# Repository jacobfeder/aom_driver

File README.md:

# 2-Tone AOM driver
This custom acousto-optic modulator (AOM) driver PCB is designed for generating short light pulses with enhanced isolation and power stability compared to traditional AOM configurations.

# Background
When generating light pulses with an AOM, two parameters that you may care about are the isolation and power stability.

The isolation (usually expressed in dB) is defined as $10*\log_{10}(P_{on} / P_{off})$, where $P_{on}$ is the transmitted optical power with the AOM enabled, and $P_{off}$ is the transmitted optical power with the AOM disabled. A low isolation means that even when the AOM is disabled, there is significant light leakage through the AOM, which can be undesirable for certain applications.

Power stability is the change in transmitted optical power as a function of time or AOM duty cycle. The active area of an AOM that the optical beam passes through is made of a material whose optical index of refraction changes with strain (acoustic waves), producing the desired beam diffraction. However, other variables, such as temperature, can impact the index of refraction and, therefore, the pointing stability of the beam.

Many traditional AOM drivers are used as follows:
- The driver produces a single frequency which is toggled on and off, often with relatively low isolation.
- The optical power is switched between being primarily concentrated in the 0th order diffraction peak (AOM disabled, RF off) and the 1st order peak (AOM enabled, RF on).

This configuration produces two undesirable effects. First, drivers with low isolation (RF power $P_{on}/P_{off}$) can limit the optical isolation of the AOM due to parasitic driving of the AOM with RF leakage. Second, when switching the RF drive on/off, there is a change in RF power dissipation in the AOM crystal, inducing a temperature change. This temperature change reduces the beam pointing stability and produces power fluctuations as a function of time and switching duty cycle.

# Overview

The 2-Tone AOM driver greatly mitigates isolation and power stability issues. Whereas traditional AOM drivers rapidly switch between an RF signal being on or off, this driver rapidly switches between two different RF frequencies. The optical power diffracted by the AOM with low-frequency drive should ideally be fiber coupled into a single-mode fiber and then used in your down-stream application. The optical power diffracted by the AOM with the high-frequency "dummy" drive should be sent into a beam-dump. If the power of the two frequencies produced by this driver are properly calibrated, thermalization effects of the AOM crystal can be minimized because the RF power delivered to the crystal is equal for both frequencies. The driver can switch between these two frequencies with very high RF isolation such that the achievable AOM optical isolation will likely become limited by the physics of gaussian optics (see additional notes below).

# Specifications
- RF isolation ~90dB
- Both frequency outputs individually tunable from ~0dBm to <-30dBm (before amplifier, >30dBm after amplifier)
- Frequency range accessible with default VCO 140 - 250 MHz (much larger range possible by swapping VCO, see customization section)
- At the time of writing, cost is <$1000 for all parts
- Convenient DIN rail mounting
- TTL input switches between the two frequencies

# Principle of Operation
The driver consists of four main parts: two nearly-identical frequency synthesis sections, a fast RF switch to select the frequency, and an (off board) RF amplifier. The frequency synthesis sections begin with a voltage-controlled oscillator (VCO) that generates the initial RF signal (CVCO55xx). A fixed attenuator limits the maximum output power (PAT1220-C-x). Next, an amplifier increases the output power (GVA-81). A voltage-variable attenuator (VVA) allows the user to tune the output power of each frequency synthesis channel in real-time using a potentiometer in order to calibrate the system (RVA-3000R). A filter reduces some of the harmonics (RLP-xxx+). An RF switch (M3SWA-2-50DRB+) for each frequency synthesis channel toggles the frequency on/off before the final switch in order to increase isolation. This concludes the frequency synthesis sections. A final RF switch (M3SWA-2-50DRB+) selects the output frequency channel. The AOM driver output is intended to then be fed to an external RF amplifier.

# Required Parts
- The 2-tone AOM driver PCB (see aom_driver.csv for PCB BOM)
- +-15V DC power supply for the AOM driver PCB, recommend TODO
- RF amplifier, recommend [Minicircuits ZHL-03-5WF+](https://www.minicircuits.com/WebStore/dashboard.html?model=ZHL-03-5WF%2B)
- 24V DC power supply for the RF amplifier, recommend TODO

# Calibration
The goal of calibration is to adjust the output power of the two driver frequency channels such that they deliver the same RF power to the AOM crystal, minimizing power fluctuations due to thermalization. A good starting point is to measure the $S_{11}$ of the AOM itself using a network analyzer, and pick your two RF frequencies to have a similar $S_{11}$. Keeping the frequencies as far apart as possible may be important to maximize optical isolation (see additional notes section). Once the frequencies are selected, set up the whole system to drive the AOM. First, the primary frequency that will be used in your downstream application should be adjusted using the potentiometer to get the desired output RF power for the desired AOM diffraction efficiency. Keep in mind that using higher power will generally tend to exacerbate thermalization issues. Next, disconnect the driver PCB from the RF power amp and measure the output power of the driver PCB. Adjust the second "dummy" frequency to have similar power to the primary frequency. At this point, the two frequencies should be delivering pretty similar heat loads to the AOM. Final tuning can be performed by observing the pulse characteristics using a photodiode (with sufficient bandwidth). Connect the photodiode to an oscilloscope and toggle the AOM with very long period (e.g. 1 minute). You should be able to observe a fast rise (ns-scale, due to the AOM acoustic wave propagation), followed by a very slow drift (seconds-scale, due to thermalization). Now, finely adjust the dummy frequency until the the slow drift is minimized.

# Customization
The driver is designed to be easily customized. The critical components were chosen such that they can be swapped out with pin-pin compatible components with different characteristics.

### Frequency
The VCO can be substituted for nearly any member of the [Crystek CVCO55 series](https://www.crystek.com/home/vco/cvco55.aspx), which should accomodate a widge range of AOM drive frequencies. By default, the schematic is configured to output 150 MHz and 250 MHz. The VCO specified in the schematic has a range of 140 - 250 MHz. Changing the frequency in this range can be accomplished by configuring resistors $R_{5}$, $R_{6}$ for channel 1 and $R_{7}$, $R_{8}$ for channel 2. The VCO output frequency as a function of tuning voltage is given by the tuning curve in the [datasheet](https://www.crystek.com/specification/vco/CVCO55CW-0140-0250.pdf). The VCO tuning voltage is $10 \text{uA} * (R_5 + R_6)$ for channel 1, and $10 \text{uA} * (R_7 + R_8)$ for channel 2. For example, let's imagine you wanted an output frequency of 200 MHz on channel 1. The CVCO55CW-0140-0250 tuning curve shows that you would need a tuning voltage of 6 V. Then you would set $R_5 + R_6 = 6 \text{V} / 10 \text{uA} = 600 \text{kOhm}$. Similarly, resistors $R_{9}$ and $R_{10}$ set the VCO power supply voltages and can be substituted as needed according to $V_{CC1} = 10 \text{uA} * R_{9}$ and $V_{CC2} = 10 \text{uA} * R_{10}$. When changing the drive frequency, filters FL1 and FL2 should potentially be changed in order to accomodate the new frequency. They should be chosen such that the primary frequency is minimally attenuated, but harmonics are maximally attenuated. However, attenuating harmonics may not have a significant impact on the performance for reasons explained in the additional notes section.

### Power
The final RF output power of the system is impossible to predict precisely due to the tolerance stackup of all the components, which is why the board contains a potentiometer for individually tuning the output power of each frequency synthesis channel as well as a power-limiting fixed attenuator. The driver PCB should be capable of outputting a maximum power of >0dBm. The [Minicircuits ZHL-03-5WF+](https://www.minicircuits.com/WebStore/dashboard.html?model=ZHL-03-5WF%2B) has a gain of >30dB, so the final output power that can be achieved before the AOM is in excess of 1W. AOMs (and power amplifiers) can be damaged by too much input power. For this reason, a fixed attenuator PAT1220-C-x is included (U7 and U8) to limit the driver PCB maximum output power. Before connecting the driver PCB to the RF amplifier or AOM, the driver PCB output power should be measured. It is recommended to pick a specific PAT1220-C-x fixed attenuator for U7 and U8 in order to limit the maximum output power for your given RF amplifier and AOM such that no damage to either component is possible when the VVA poteniometer is tuned to output the maximum power from the driver PCB.

# Additional Notes
- The AOM driver system will cause the AOM to produce several optical beams at its output due to both AOM physics and RF design. When the low-frequency RF path is selected, it will produce 0th, 1st, 2nd, ..., nth order beams. The 1st order beam is the desired optical output and should go to the downstream application. All other 0th, 2nd, etc. order beams should be blocked or otherwise not coupled into the optical output. When the high frequency is selected, it will also produce 0th, 1st, 2nd, ..., nth order beams. All of these beams are "dummy" beams and should be blocked or otherwise not coupled into the downstream application. It is important to use the 1st order low-frequency beam for your application, as it will have minimal interference from RF drive harmonics.
- While the AOM driver has very high RF isolation, achieving high optical isolation requires additional careful attention to detail with optical design. I would recommend fiber coupling the 1st order low-frequency beam after the AOM for best performance.
- If all beams except the low-frequency 1st order beam are sufficiently blocked, the optical isolation will likely become limited by gaussian optics considerations. A beam of light entering the AOM will always have some finite divergence. After exiting the AOM, many beams are generated as explained above. These undesired beams will always have some degree of coupling into the desired output path due to their finite divergence, limiting the total optical isolation. A script is provided (TODO) to help with calculating the optical isolation. There is a somewhat intuitive explanation for this optics-limited isolation by consdering the tradeoff between isolation, rise-time, and AOM RF bandwidth. Getting a faster rise-time requires a smaller optical spot size on the AOM crystal, which requires a higher beam divergence. Higher divergence results in reduced isolation as explained above. Higher AOM RF bandwidth allows the primary and "dummy" beams to be separated by a larger angle, which increases their isolation. Therefore, it is important to consider the RF bandwidth when selecting an AOM, and the desired isolation and rise-time when selecting lenses to focus the beam onto the AOM crystal.

Feel free to email me if you have any questions at <jacobsfeder@gmail.com>.

# Acknowledgements
- This project would not have been possible without the help of Arron Campi at Gooch and Housego. He graciously provided his time and insight by helping me to understand AOM physics and limitations, as well as suggesting the idea of driving the AOM with multiple frequencies.
- Ben Soloway contributed the script that calculates optical isolation, and provided comic relief in addition to being my scientific partner in crime.
- The Awschalom Lab at UChicago and the NSF provided financial support.

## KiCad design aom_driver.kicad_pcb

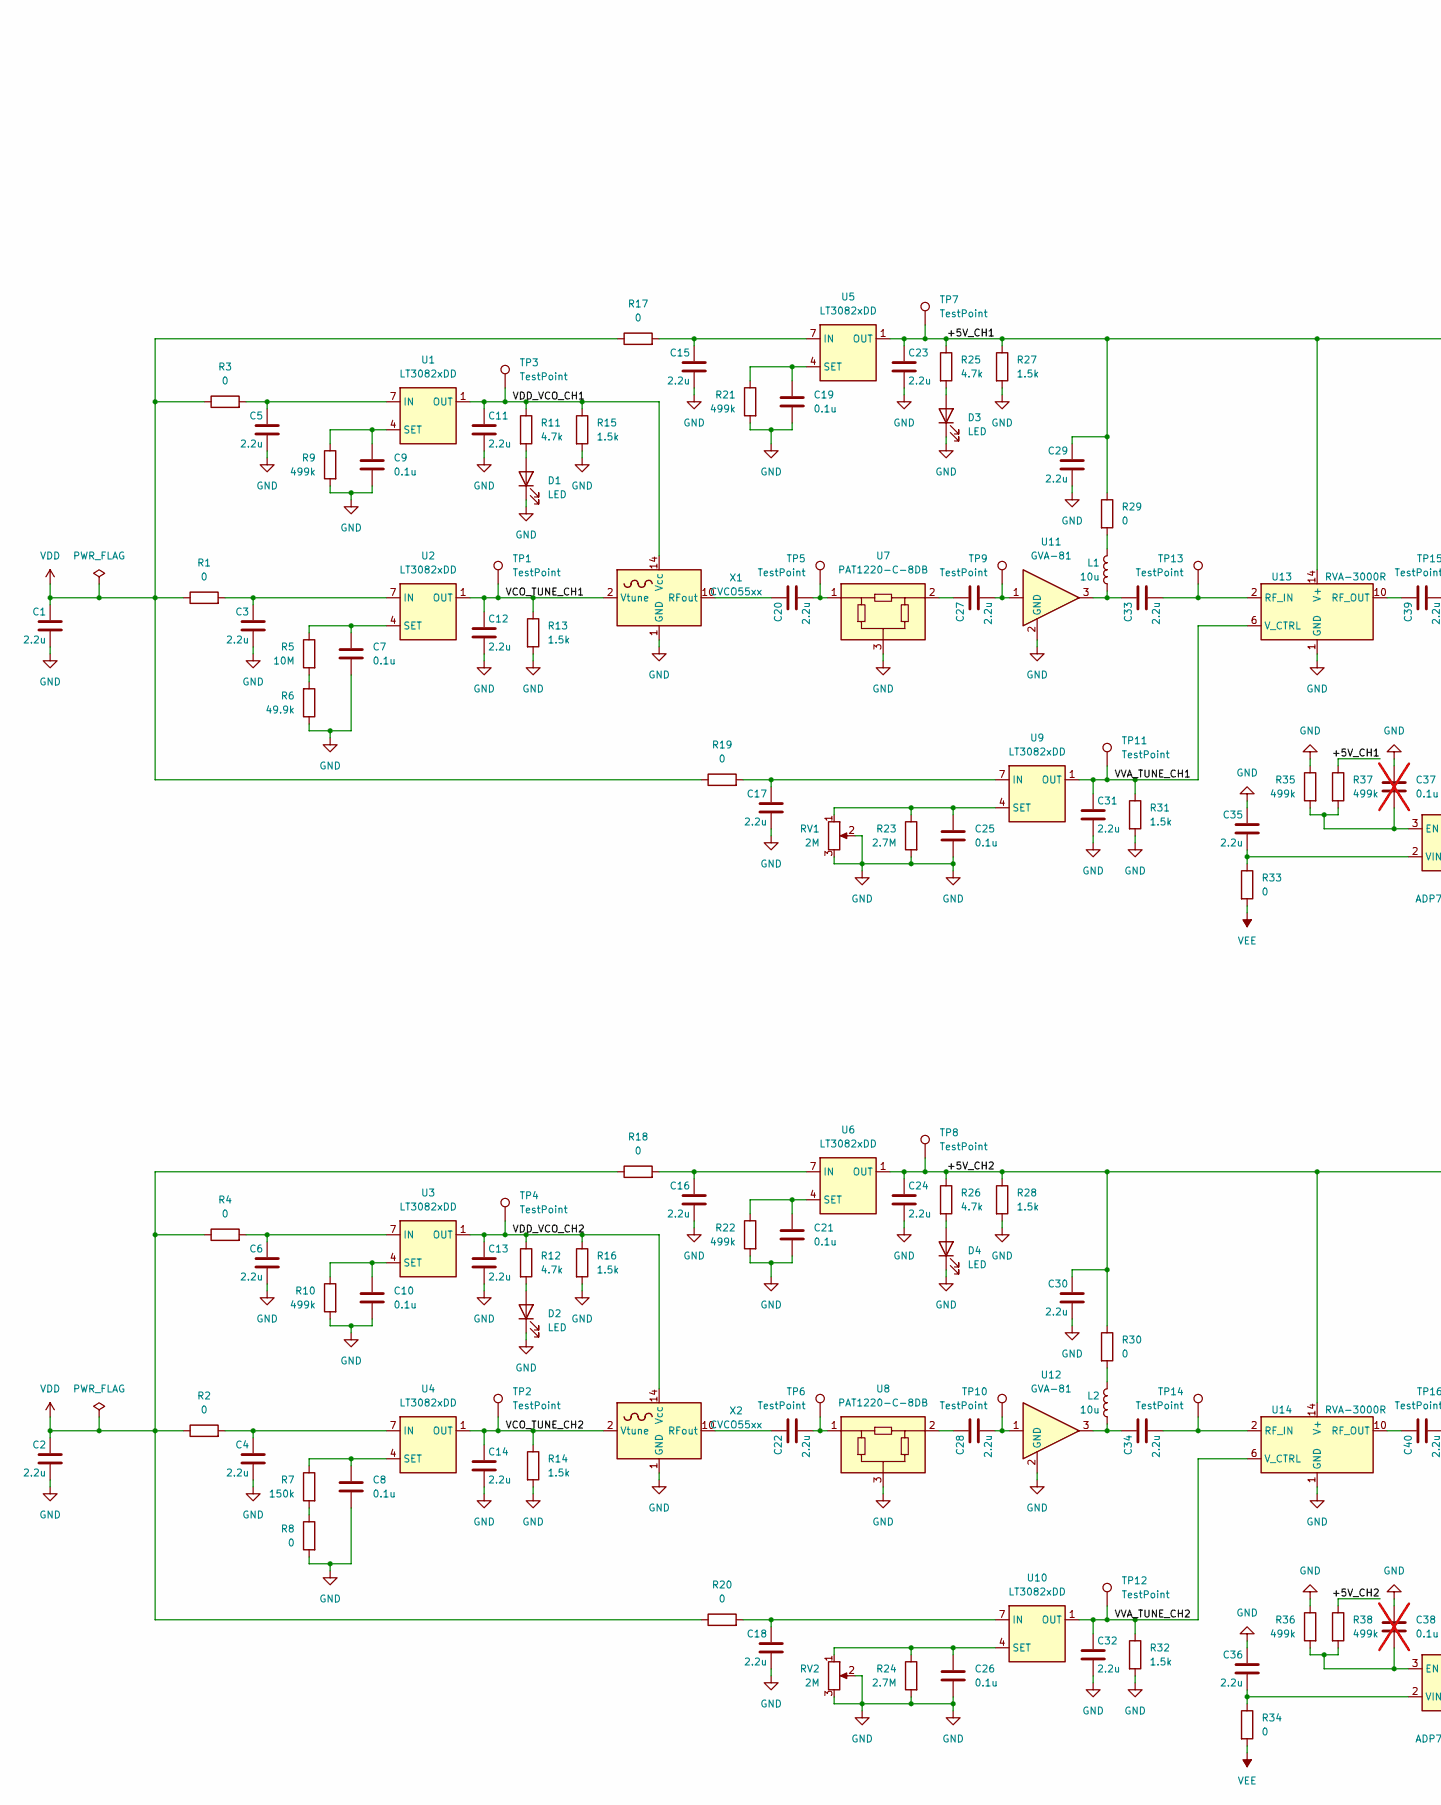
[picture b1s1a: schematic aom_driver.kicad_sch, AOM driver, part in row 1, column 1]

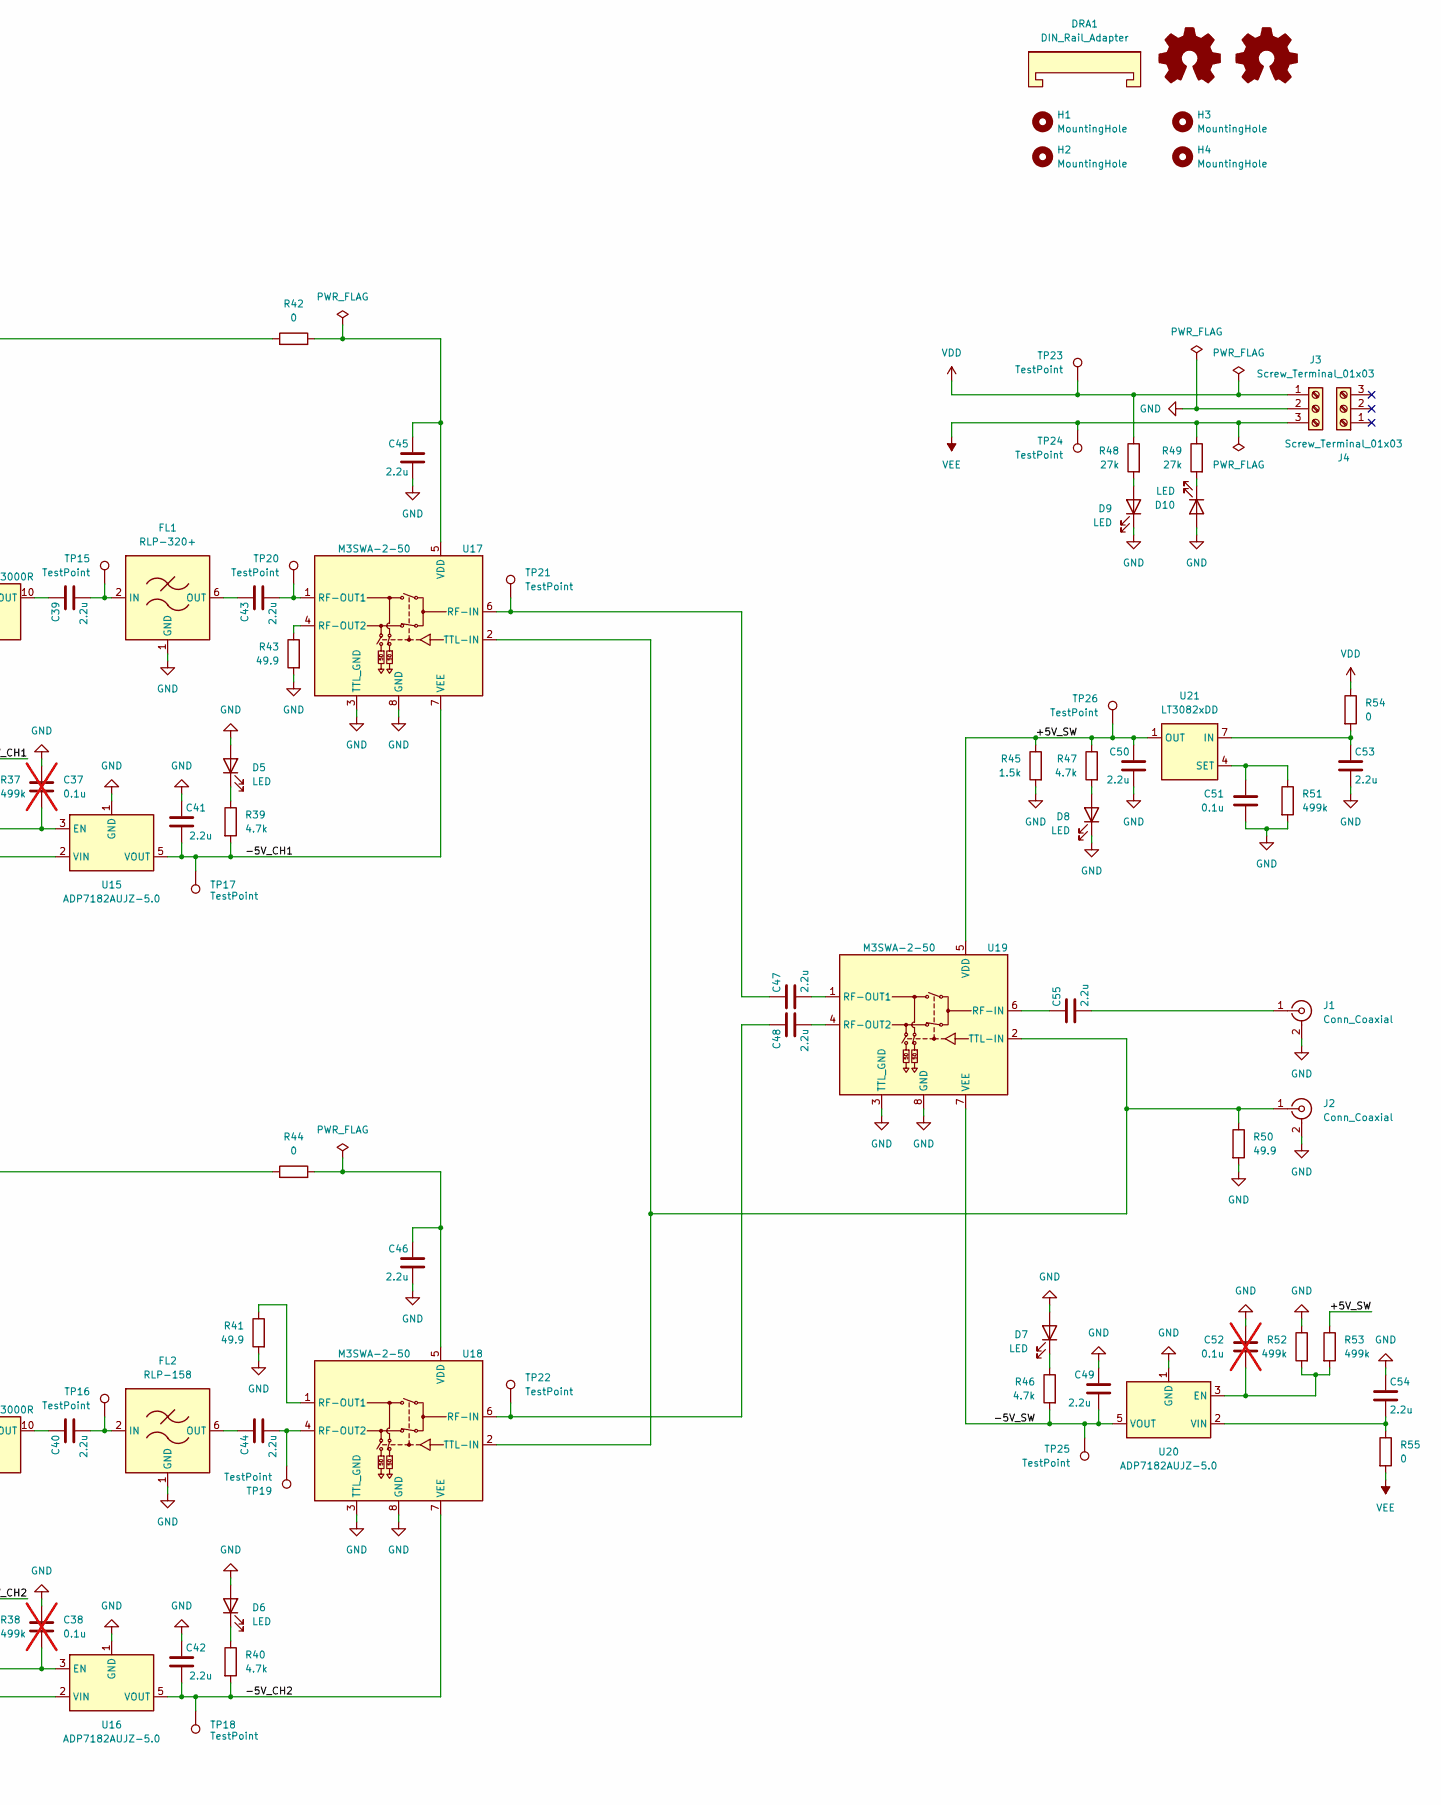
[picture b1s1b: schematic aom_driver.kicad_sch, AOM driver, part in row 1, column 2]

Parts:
C1, C2, C3, C4, C5, C6, C11, C12, C13, C14, C15, C16, C17, C18, C20, C22, C23, C24, C27, C28, C29, C30, C31, C32, C33, C34, C35, C36, C39, C40, C41, C42, C43, C44, C45, C46, C47, C48, C49, C50, C53, C54, C55: 2.2u; C_0805_2012Metric_Pad1.18x1.45mm_HandSolder
C7, C8, C9, C10, C19, C21, C25, C26, C51: 0.1u; C_0805_2012Metric_Pad1.18x1.45mm_HandSolder
C37, C38, C52: 0.1u; C_0805_2012Metric_Pad1.18x1.45mm_HandSolder; not fitted
D1, D2, D3, D4, D5, D6, D7, D8, D9, D10: LED; LED_0603_1608Metric_Pad1.05x0.95mm_HandSolder
DRA1: DIN_Rail_Adapter
FL1: RLP-320+; Mini-Circuits_GP731_LandPatternPL-176
FL2: RLP-158; Mini-Circuits_GP731_LandPatternPL-176
H1, H2, H3, H4: MountingHole; MountingHole_4.3mm_M4_DIN965
J1, J2: Conn_Coaxial; SMA_Samtec_SMA-J-P-X-ST-EM1_EdgeMount
J3: Screw_Terminal_01x03; PhoenixContact_MSTBA_2,5_3-G-5,08_1x03_P5.08mm_Horizontal
J4: Screw_Terminal_01x03
L1, L2: 10u; L_0805_2012Metric_Pad1.05x1.20mm_HandSolder
R1, R2, R3, R4, R8, R17, R18, R19, R20, R29, R30, R33, R34, R42, R44, R54, R55: 0; R_0805_2012Metric_Pad1.20x1.40mm_HandSolder
R5: 10M; R_0805_2012Metric_Pad1.20x1.40mm_HandSolder
R6: 49.9k; R_0805_2012Metric_Pad1.20x1.40mm_HandSolder
R7: 150k; R_0805_2012Metric_Pad1.20x1.40mm_HandSolder
R9, R10, R21, R22, R35, R36, R37, R38, R51, R52, R53: 499k; R_0805_2012Metric_Pad1.20x1.40mm_HandSolder
R11, R12, R25, R26, R39, R40, R46, R47: 4.7k; R_0805_2012Metric_Pad1.20x1.40mm_HandSolder
R13, R14, R15, R16, R27, R28, R31, R32, R45: 1.5k; R_0805_2012Metric_Pad1.20x1.40mm_HandSolder
R23, R24: 2.7M; R_0805_2012Metric_Pad1.20x1.40mm_HandSolder
R41, R43, R50: 49.9; R_0805_2012Metric_Pad1.20x1.40mm_HandSolder
R48, R49: 27k; R_0805_2012Metric_Pad1.20x1.40mm_HandSolder
RV1, RV2: 2M; Potentiometer_Bourns_3296X_Horizontal
SYM1: Logo_Open_Hardware_Small; OSHW-Logo2_9.8x8mm_SilkScreen
SYM2: Logo_Open_Hardware_Small; KiCad-Logo2_5mm_SilkScreen
TP1, TP2, TP3, TP4, TP5, TP6, TP7, TP8, TP9, TP10, TP11, TP12, TP13, TP14, TP15, TP16, TP17, TP18, TP19, TP20, TP21, TP22, TP23, TP24, TP25, TP26: TestPoint; TestPoint_Pad_D2.0mm
U1, U2, U3, U4, U5, U6, U9, U10, U21: LT3082xDD; DFN-8-1EP_3x3mm_P0.5mm_EP1.66x2.38mm
U7, U8: PAT1220-C-8DB; RF_Attenuator_Susumu_PAT1220
U11, U12: GVA-81; SOT-89-3
U13, U14: RVA-3000R; Mini-Circuits_DV874_LandPatternPL-040
U15, U16, U20: ADP7182AUJZ-5.0; TSOT-23-5
U17, U18, U19: M3SWA-2-50; Mini-Circuits_DL805
X1, X2: CVCO55xx; Mini-Circuits_CK605_LandPatternPL-012

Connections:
/+5V_CH1: C23.1, C29.1, R25.1, R27.1, R29.1, R37.1, R42.1, TP7.1, U5.1 (OUT), U5.2 (OUT), U5.9 (OUT), U13.14 (V+)
/+5V_CH2: C24.1, C30.1, R26.1, R28.1, R30.1, R38.1, R44.1, TP8.1, U6.1 (OUT), U6.2 (OUT), U6.9 (OUT), U14.14 (V+)
/+5V_SW: C50.1, R45.1, R47.1, R53.1, TP26.1, U19.5 (VDD), U21.1 (OUT), U21.2 (OUT), U21.9 (OUT)
/-5V_CH1: C41.2, R39.2, TP17.1, U15.5 (VOUT), U17.7 (VEE)
/-5V_CH2: C42.2, R40.2, TP18.1, U16.5 (VOUT), U18.7 (VEE)
/-5V_SW: C49.2, R46.2, TP25.1, U19.7 (VEE), U20.5 (VOUT)
/VCO_TUNE_CH1: C12.1, R13.1, TP1.1, U2.1 (OUT), U2.2 (OUT), U2.9 (OUT), X1.2 (Vtune)
/VCO_TUNE_CH2: C14.1, R14.1, TP2.1, U4.1 (OUT), U4.2 (OUT), U4.9 (OUT), X2.2 (Vtune)
/VDD_VCO_CH1: C11.1, R11.1, R15.1, TP3.1, U1.1 (OUT), U1.2 (OUT), U1.9 (OUT), X1.14 (Vcc)
/VDD_VCO_CH2: C13.1, R12.1, R16.1, TP4.1, U3.1 (OUT), U3.2 (OUT), U3.9 (OUT), X2.14 (Vcc)
/VVA_TUNE_CH1: C31.1, R31.1, TP11.1, U9.1 (OUT), U9.2 (OUT), U9.9 (OUT), U13.6 (V_CTRL)
/VVA_TUNE_CH2: C32.1, R32.1, TP12.1, U10.1 (OUT), U10.2 (OUT), U10.9 (OUT), U14.6 (V_CTRL)
GND: C1.2, C2.2, C3.2, C4.2, C5.2, C6.2, C7.2, C8.2, C9.2, C10.2, C11.2, C12.2, C13.2, C14.2, C15.2, C16.2, C17.2, C18.2, C19.2, C21.2, C23.2, C24.2, C25.2, C26.2, C29.2, C30.2, C31.2, C32.2, C35.1, C36.1, C37.1, C38.1, C41.1, C42.1, C45.2, C46.2, C49.1, C50.2, C51.2, C52.1, C53.2, C54.1, D1.1 (K), D2.1 (K), D3.1 (K), D4.1 (K), D5.2 (A), D6.2 (A), D7.2 (A), D8.1 (K), D9.1 (K), D10.2 (A), FL1.1 (GND), FL1.3 (GND), FL1.4 (GND), FL1.5 (GND), FL1.7 (GND), FL1.8 (GND), FL2.1 (GND), FL2.3 (GND), FL2.4 (GND), FL2.5 (GND), FL2.7 (GND), FL2.8 (GND), J1.2 (Ext), J2.2 (Ext), J3.2, R6.1, R8.2, R9.2, R10.2, R13.2, R14.2, R15.2, R16.2, R21.2, R22.2, R23.2, R24.2, R27.2, R28.2, R31.2, R32.2, R35.1, R36.1, R41.2, R43.2, R45.2, R50.2, R51.2, R52.1, RV1.2, RV1.3, RV2.2, RV2.3, U7.3, U8.3, U11.2 (GND), U12.2 (GND), U13.1 (GND), U13.3 (GND), U13.4 (GND), U13.5 (GND), U13.7 (GND), U13.8 (GND), U13.9 (GND), U13.11 (GND), U13.12 (GND), U13.13 (GND), U13.15 (GND), U13.16 (GND), U14.1 (GND), U14.3 (GND), U14.4 (GND), U14.5 (GND), U14.7 (GND), U14.8 (GND), U14.9 (GND), U14.11 (GND), U14.12 (GND), U14.13 (GND), U14.15 (GND), U14.16 (GND), U15.1 (GND), U16.1 (GND), U17.3 (TTL_GND), U17.8 (GND), U17.9 (GND), U18.3 (TTL_GND), U18.8 (GND), U18.9 (GND), U19.3 (TTL_GND), U19.8 (GND), U19.9 (GND), U20.1 (GND), X1.1 (GND), X1.3 (GND), X1.4 (GND), X1.5 (GND), X1.6 (GND), X1.7 (GND), X1.8 (GND), X1.9 (GND), X1.11 (GND), X1.12 (GND), X1.13 (GND), X1.15 (GND), X1.16 (GND), X2.1 (GND), X2.3 (GND), X2.4 (GND), X2.5 (GND), X2.6 (GND), X2.7 (GND), X2.8 (GND), X2.9 (GND), X2.11 (GND), X2.12 (GND), X2.13 (GND), X2.15 (GND), X2.16 (GND)
unnamed: C3.1, R1.2, U2.7 (IN), U2.8 (IN)
unnamed: C4.1, R2.2, U4.7 (IN), U4.8 (IN)
unnamed: C5.1, R3.2, U1.7 (IN), U1.8 (IN)
unnamed: C6.1, R4.2, U3.7 (IN), U3.8 (IN)
unnamed: C15.1, R17.2, U5.7 (IN), U5.8 (IN)
unnamed: C16.1, R18.2, U6.7 (IN), U6.8 (IN)
unnamed: C17.1, R19.2, U9.7 (IN), U9.8 (IN)
unnamed: C18.1, R20.2, U10.7 (IN), U10.8 (IN)
unnamed: C20.2, TP5.1, U7.1
unnamed: C22.2, TP6.1, U8.1
unnamed: C27.1, U7.2
unnamed: C27.2, TP9.1, U11.1
unnamed: C28.1, U8.2
unnamed: C28.2, TP10.1, U12.1
unnamed: C33.1, L1.2, U11.3
unnamed: C34.1, L2.2, U12.3
unnamed: C53.1, R54.2, U21.7 (IN), U21.8 (IN)
unnamed: D1.2 (A), R11.2
unnamed: D2.2 (A), R12.2
unnamed: D3.2 (A), R25.2
unnamed: D4.2 (A), R26.2
unnamed: D5.1 (K), R39.1
unnamed: D6.1 (K), R40.1
unnamed: D7.1 (K), R46.1
unnamed: D8.2 (A), R47.2
unnamed: D9.2 (A), R48.2
unnamed: D10.1 (K), R49.2
unnamed: C39.2, FL1.2 (IN), TP15.1
unnamed: C43.1, FL1.6 (OUT)
unnamed: C40.2, FL2.2 (IN), TP16.1
unnamed: C44.1, FL2.6 (OUT)
unnamed: C55.2, J1.1 (In)
unnamed: J2.1 (In), R50.1, U17.2 (TTL-IN), U18.2 (TTL-IN), U19.2 (TTL-IN)
unnamed: L1.1, R29.2
unnamed: L2.1, R30.2
unnamed: R5.2, R6.2
unnamed: R7.2, R8.1
unnamed: C9.1, R9.1, U1.4 (SET)
unnamed: C7.1, R5.1, U2.4 (SET)
unnamed: C10.1, R10.1, U3.4 (SET)
unnamed: C8.1, R7.1, U4.4 (SET)
unnamed: C19.1, R21.1, U5.4 (SET)
unnamed: C21.1, R22.1, U6.4 (SET)
unnamed: C25.1, R23.1, RV1.1, U9.4 (SET)
unnamed: C26.1, R24.1, RV2.1, U10.4 (SET)
unnamed: C33.2, TP13.1, U13.2 (RF_IN)
unnamed: C39.1, U13.10 (RF_OUT)
unnamed: C34.2, TP14.1, U14.2 (RF_IN)
unnamed: C40.1, U14.10 (RF_OUT)
unnamed: C37.2, R35.2, R37.2, U15.3 (EN)
unnamed: C35.2, R33.1, U15.2 (VIN)
unnamed: C38.2, R36.2, R38.2, U16.3 (EN)
unnamed: C36.2, R34.1, U16.2 (VIN)
unnamed: C47.1, TP21.1, U17.6 (RF-IN)
unnamed: C43.2, TP20.1, U17.1 (RF-OUT1)
unnamed: R43.1, U17.4 (RF-OUT2)
unnamed: C45.1, R42.2, U17.5 (VDD)
unnamed: C48.1, TP22.1, U18.6 (RF-IN)
unnamed: R41.1, U18.1 (RF-OUT1)
unnamed: C44.2, TP19.1, U18.4 (RF-OUT2)
unnamed: C46.1, R44.2, U18.5 (VDD)
unnamed: C55.1, U19.6 (RF-IN)
unnamed: C47.2, U19.1 (RF-OUT1)
unnamed: C48.2, U19.4 (RF-OUT2)
unnamed: C52.2, R52.2, R53.2, U20.3 (EN)
unnamed: C54.2, R55.1, U20.2 (VIN)
unnamed: C51.1, R51.1, U21.4 (SET)
unnamed: C20.1, X1.10 (RFout)
unnamed: C22.1, X2.10 (RFout)
VDD: C1.1, C2.1, J3.1, R1.1, R2.1, R3.1, R4.1, R17.1, R18.1, R19.1, R20.1, R48.1, R54.1, TP23.1
VEE: J3.3, R33.2, R34.2, R49.1, R55.2, TP24.1

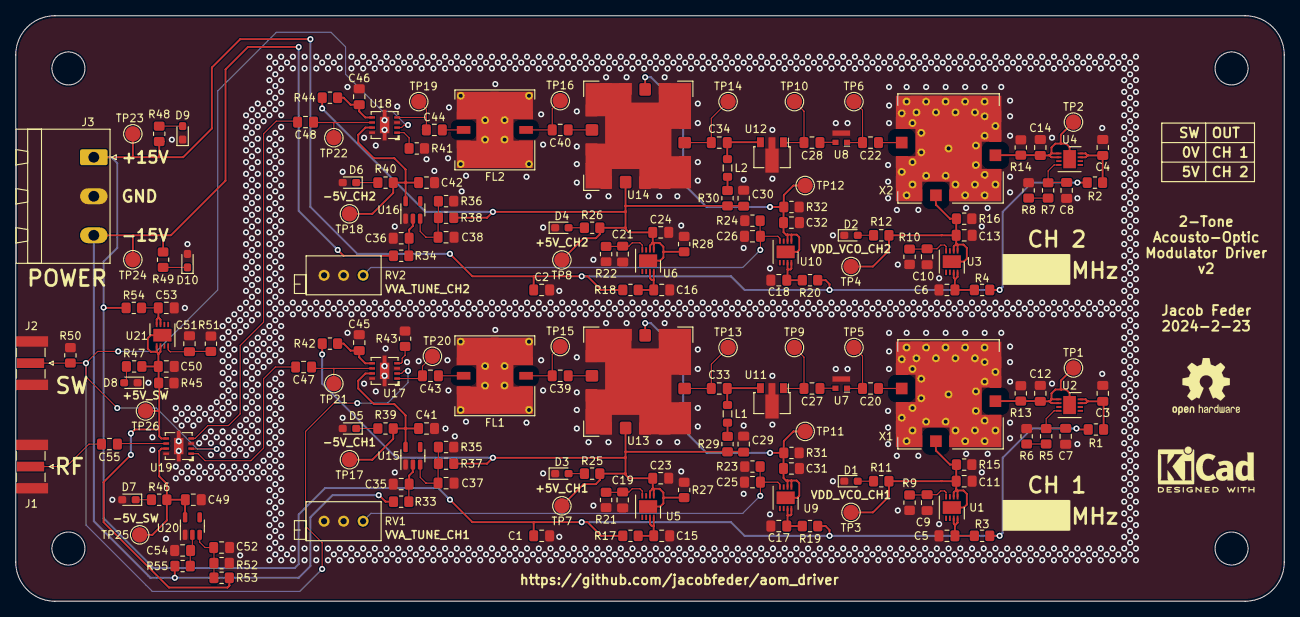
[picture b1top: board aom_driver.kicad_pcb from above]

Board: 4 copper layers, 165.1 x 76.2 mm, 184 parts (0 on the bottom side), 84 nets.

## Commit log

2024-02-13 use CERN license
2024-02-13 v1 design
2024-02-24 Add details to README; add PCB BOM, schematic, PCB image
2024-02-24 add PCB image to README
2024-02-25 README corrections
2024-02-25 add PCB schematic
2024-02-25 revert AOM PCB schematic in README
2024-02-25 regenerate gerbers to include paste file
2024-02-25 add calibration section to README
